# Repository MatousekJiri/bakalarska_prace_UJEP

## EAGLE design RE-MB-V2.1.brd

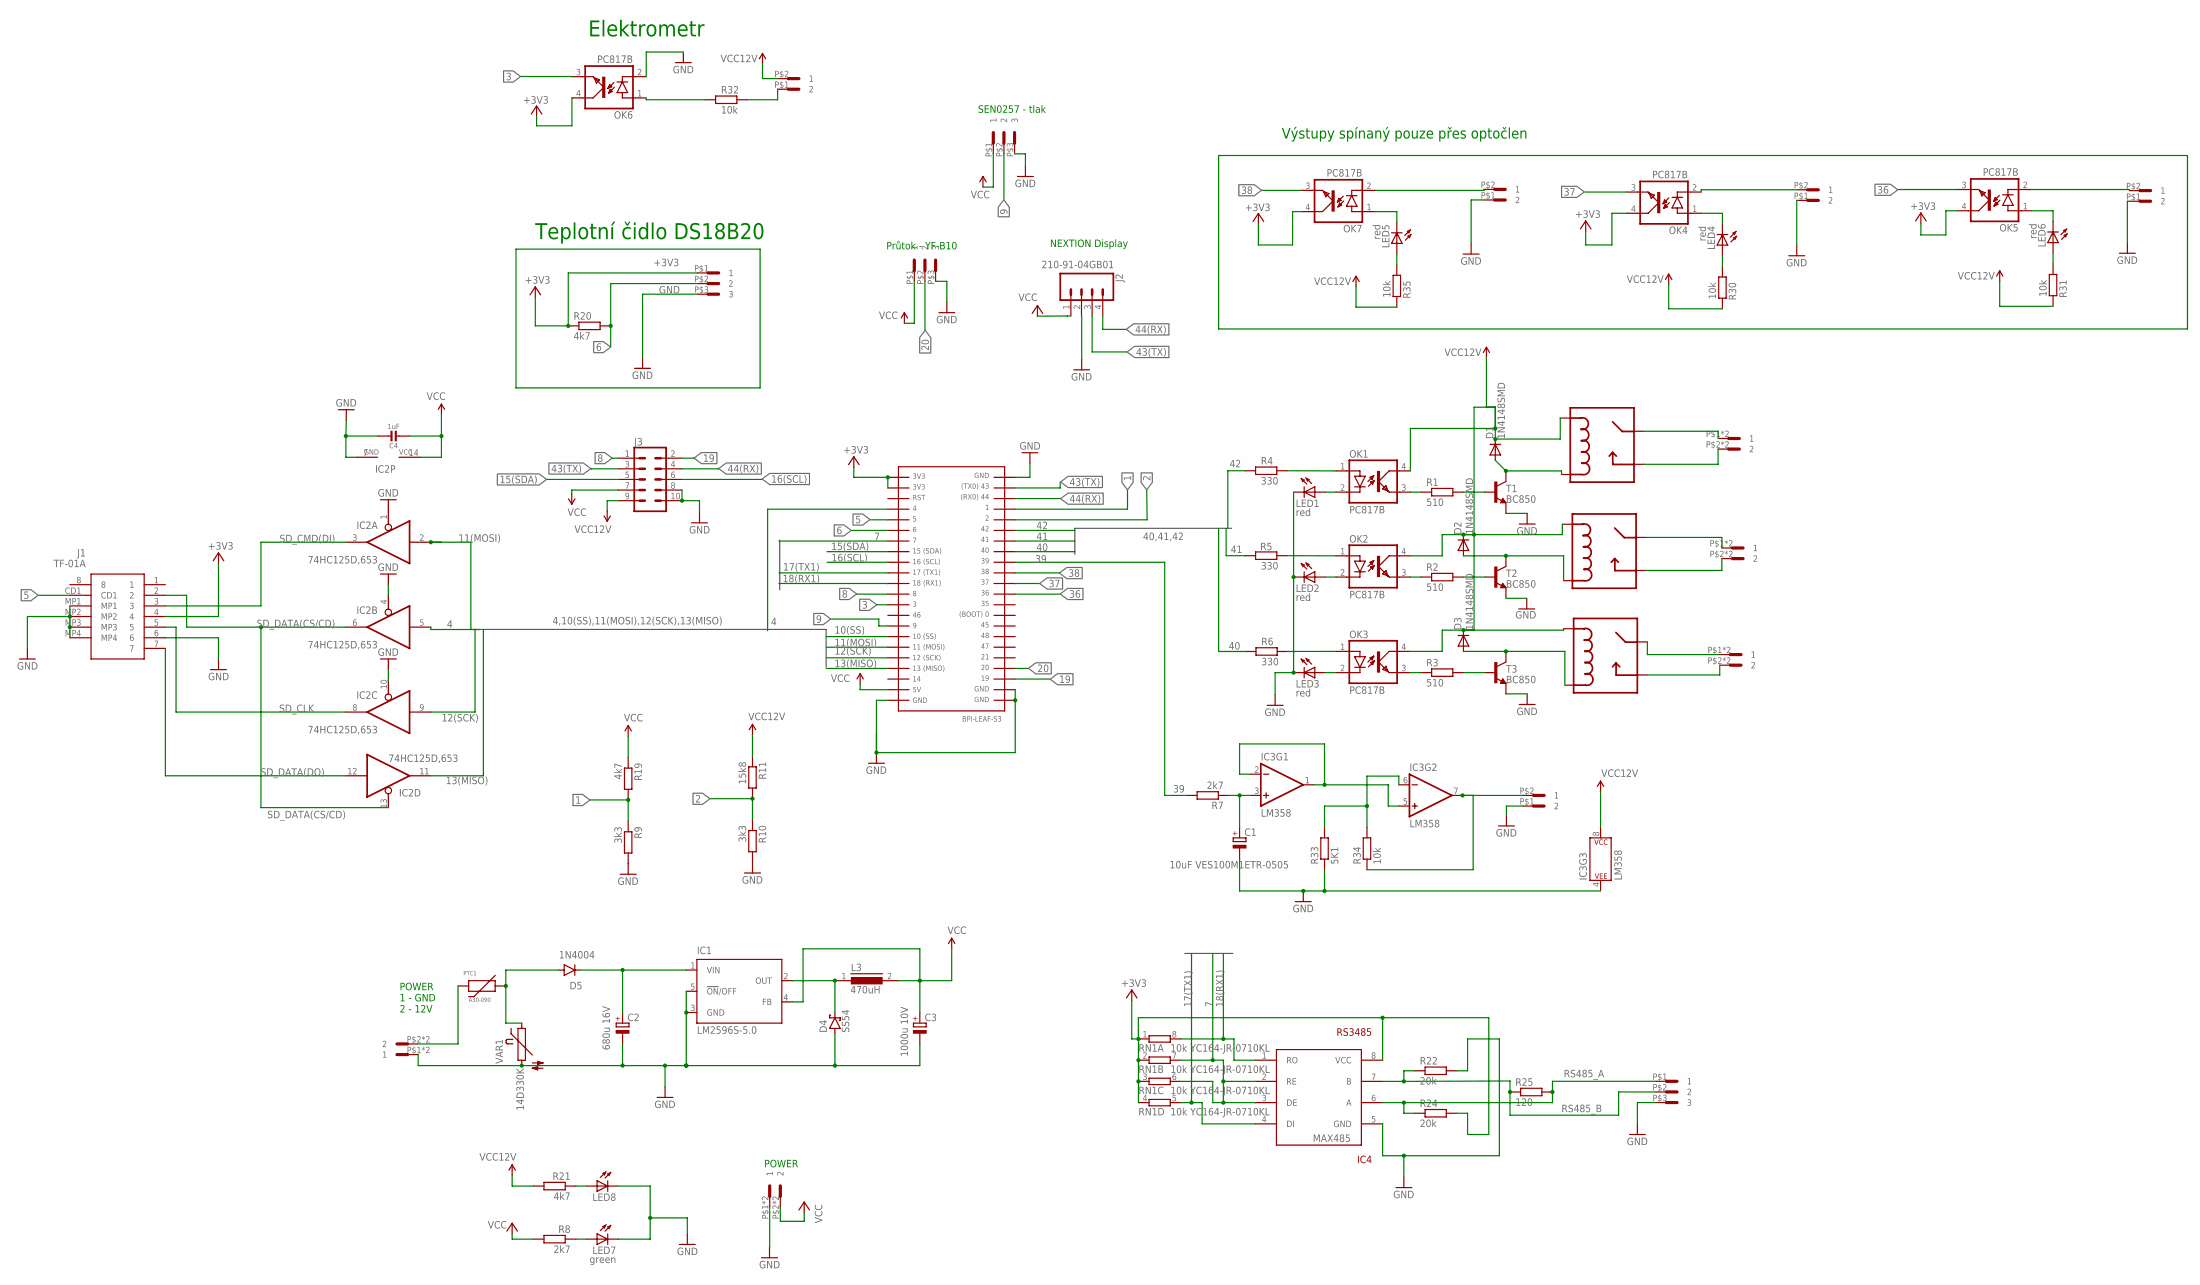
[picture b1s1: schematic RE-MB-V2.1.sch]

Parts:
BPI: BPI-LEAF-S3
C1: 10uF VES100M1ETR-0505; PANASONIC_C
C2: 680u 16V; 153CLV-1010
C3: 1000u 10V; 153CLV-1010
C4: 1uF; 0805-NO
D1, D2, D3: 1N4148SMD; DO214AC
D4: SS54; SMB
D5: 1N4004; DO41-10
IC1: LM2596S-5.0; TO263-5
IC2: 74HC125D,653; SO14
IC3: LM358; SO08
IC4: RS3485; MAX485
J1: TF-01A; TF01A
J2: 210-91-04GB01; 1X04
J3: CONN_05X2RAF; 2X5-RAF
K1, K2, K3: HF49FD/012-1H11; HF49FD/024-1H11
L3: 470uH; DR127
LED1, LED2, LED3, LED4, LED5, LED6: red; CHIPLED_0805
LED7, LED8: green; CHIPLED_0805
OK1, OK2, OK3, OK4, OK5, OK6, OK7: PC817B; DIL04
PTC1: A30-090; PK250-240
R1, R2, R3: 510; M0805
R4, R5, R6: 330; M0805
R7: 2k7; R0805
R8: 2k7; M0805
R9, R10: 3k3; M0805
R11: 15k8; M0805
R19, R20, R21: 4k7; M0805
R22, R24: 20k; R0805
R25: 120; R0805
R30, R31, R32, R35: 10k; M0805
R33: 5K1; R0805
R34: 10k; R0805
RN1: 10k YC164-JR-0710KL; 0603-ARV
T1, T2, T3: BC850; SOT23
U$2, U$4, U$5, U$6, U$7: DG235-5.0
U$3, U$10, U$12, U$16: SPTA1/3-5,0
U$8, U$9, U$13, U$14, U$15: SPTA1/2-5,0
VAR1: 14D330K; S10K11

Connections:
1: BPI.26, R9.1, R19.2
2: BPI.27, R10.1, R11.2
3: BPI.13, OK6.3 (EMIT)
4: BPI.4, IC2.5 (I)
5: BPI.5, J1.CD1
6: BPI.6, R20.2, U$3.P$2 (2)
7: BPI.7, IC4.2 (RE), IC4.3 (DE), RN1.6 (2), RN1.7 (2)
8: BPI.12, J3.1
9: BPI.15, U$12.P$2 (2)
10(SS): BPI.16
11(MOSI): BPI.17, IC2.2 (I)
12(SCK): BPI.18, IC2.9 (I)
13(MISO): BPI.19, IC2.11 (O)
15(SDA): BPI.8, J3.5
16(SCL): BPI.9, J3.6
17(TX1): BPI.10, IC4.4 (DI), RN1.5 (2)
18(RX1): BPI.11, IC4.1 (RO), RN1.8 (2)
19: BPI.42, J3.2
20: BPI.41, U$16.P$2 (2)
36: BPI.34, OK5.3 (EMIT)
37: BPI.33, OK4.3 (EMIT)
38: BPI.32, OK7.3 (EMIT)
39: BPI.31, R7.2
40: BPI.30, R6.1
41: BPI.29, R5.1
42: BPI.28, R4.1
43(TX): BPI.24, J2.3, J3.3
44(RX): BPI.25, J2.4, J3.4
+3V3: BPI.1, BPI.2, IC4.8 (VCC), J1.4, OK4.4 (COL), OK5.4 (COL), OK6.4 (COL), OK7.4 (COL), R20.1, R24.2, RN1.1, RN1.2 (1), RN1.3 (1), RN1.4 (1), U$3.P$1 (1)
GND: BPI.22, BPI.23, BPI.43, BPI.44, C1.-, C2.-, C3.-, C4.2, D4.A, IC1.3 (GND), IC1.5 (!ON!/OFF), IC2.1 (OE), IC2.4 (OE), IC2.7 (GND), IC2.10 (OE), IC3.4 (P$V-), IC4.5 (GND), J1.6, J1.MP1, J1.MP2, J1.MP3, J1.MP4, J2.2, J3.8, J3.10, LED1.C, LED2.C, LED3.C, LED7.C, LED8.C, OK6.2 (C), R9.2, R10.2, R22.2, R33.1, T1.2 (E), T2.2 (E), T3.2 (E), U$2.P$1 (1), U$2.P$3 (1), U$3.P$3 (3), U$6.P$1 (1), U$6.P$3 (1), U$8.P$1 (2), U$10.P$3 (3), U$12.P$3 (3), U$13.P$1 (2), U$14.P$1 (2), U$15.P$1 (2), U$16.P$3 (3), VAR1.2
GND1: OK4.2 (C), U$13.P$2 (1)
unnamed: PTC1.P$1, U$2.P$2 (2), U$2.P$4 (2)
unnamed: K1.P$1, U$4.P$1 (1), U$4.P$3 (1)
unnamed: D5.A, PTC1.P$2, VAR1.1
unnamed: K1.P$2, U$4.P$2 (2), U$4.P$4 (2)
unnamed: K2.P$1, U$5.P$1 (1), U$5.P$3 (1)
unnamed: K2.P$2, U$5.P$2 (2), U$5.P$4 (2)
unnamed: K3.P$1, U$7.P$1 (1), U$7.P$3 (1)
unnamed: K3.P$2, U$7.P$2 (2), U$7.P$4 (2)
unnamed: OK7.2 (C), U$15.P$2 (1)
unnamed: LED4.C, OK4.1 (A)
unnamed: LED4.A, R30.1
unnamed: OK5.2 (C), U$14.P$2 (1)
unnamed: LED6.C, OK5.1 (A)
unnamed: LED6.A, R31.1
unnamed: OK6.1 (A), R32.1
unnamed: LED1.A, OK1.2 (C)
unnamed: D1.A, K1.P$4, T1.3 (C)
unnamed: OK1.3 (EMIT), R1.1
unnamed: C1.+, IC3.3 (+IN), R7.1
unnamed: IC3.1 (OUT), IC3.2 (-IN), IC3.5 (+IN)
unnamed: R1.2, T1.1 (B)
unnamed: R32.2, U$9.P$1 (2)
unnamed: LED7.A, R8.1
unnamed: OK1.1 (A), R4.2
unnamed: LED8.A, R21.1
unnamed: D4.C, IC1.2 (OUT), L3.1
unnamed: IC3.6 (-IN), R33.2, R34.2
unnamed: IC3.7 (OUT), R34.1, U$8.P$2 (1)
unnamed: LED2.A, OK2.2 (C)
unnamed: LED3.A, OK3.2 (C)
unnamed: OK3.1 (A), R6.2
unnamed: OK2.1 (A), R5.2
unnamed: OK2.3 (EMIT), R2.1
unnamed: OK3.3 (EMIT), R3.1
unnamed: R3.2, T3.1 (B)
unnamed: R2.2, T2.1 (B)
unnamed: D2.A, K2.P$4, T2.3 (C)
unnamed: D3.A, K3.P$4, T3.3 (C)
unnamed: LED5.C, OK7.1 (A)
unnamed: LED5.A, R35.1
RS485_A: IC4.6 (A), R24.1, R25.2, U$10.P$1 (1)
RS485_B: IC4.7 (B), R22.1, R25.1, U$10.P$2 (2)
SD_CLK: IC2.8 (O), J1.5
SD_CMD(DI): IC2.3 (O), J1.3
SD_DATA(CS/CD): IC2.6 (O), IC2.13 (OE), J1.2
SD_DATA(DO): IC2.12 (I), J1.7
VCC: BPI.21, C3.+, C4.1, IC1.4 (FB), IC2.14 (VCC), J2.1, J3.7, L3.2, R8.2, R19.1, U$6.P$2 (2), U$6.P$4 (2), U$12.P$1 (1), U$16.P$1 (1)
VCC12V: C2.+, D1.C, D2.C, D3.C, D5.C, IC1.1 (VIN), IC3.8 (P$V+), J3.9, K1.P$3, K2.P$3, K3.P$3, OK1.4 (COL), OK2.4 (COL), OK3.4 (COL), R11.1, R21.2, R30.2, R31.2, R35.2, U$9.P$2 (1)

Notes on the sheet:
Výstupy spínaný pouze přes optočlen
Průtok - YF-B10
NEXTION Display
POWER 1 - GND 2 - 12V
Teplotní čidlo DS18B20
POWER
Elektrometr
SEN0257 - tlak

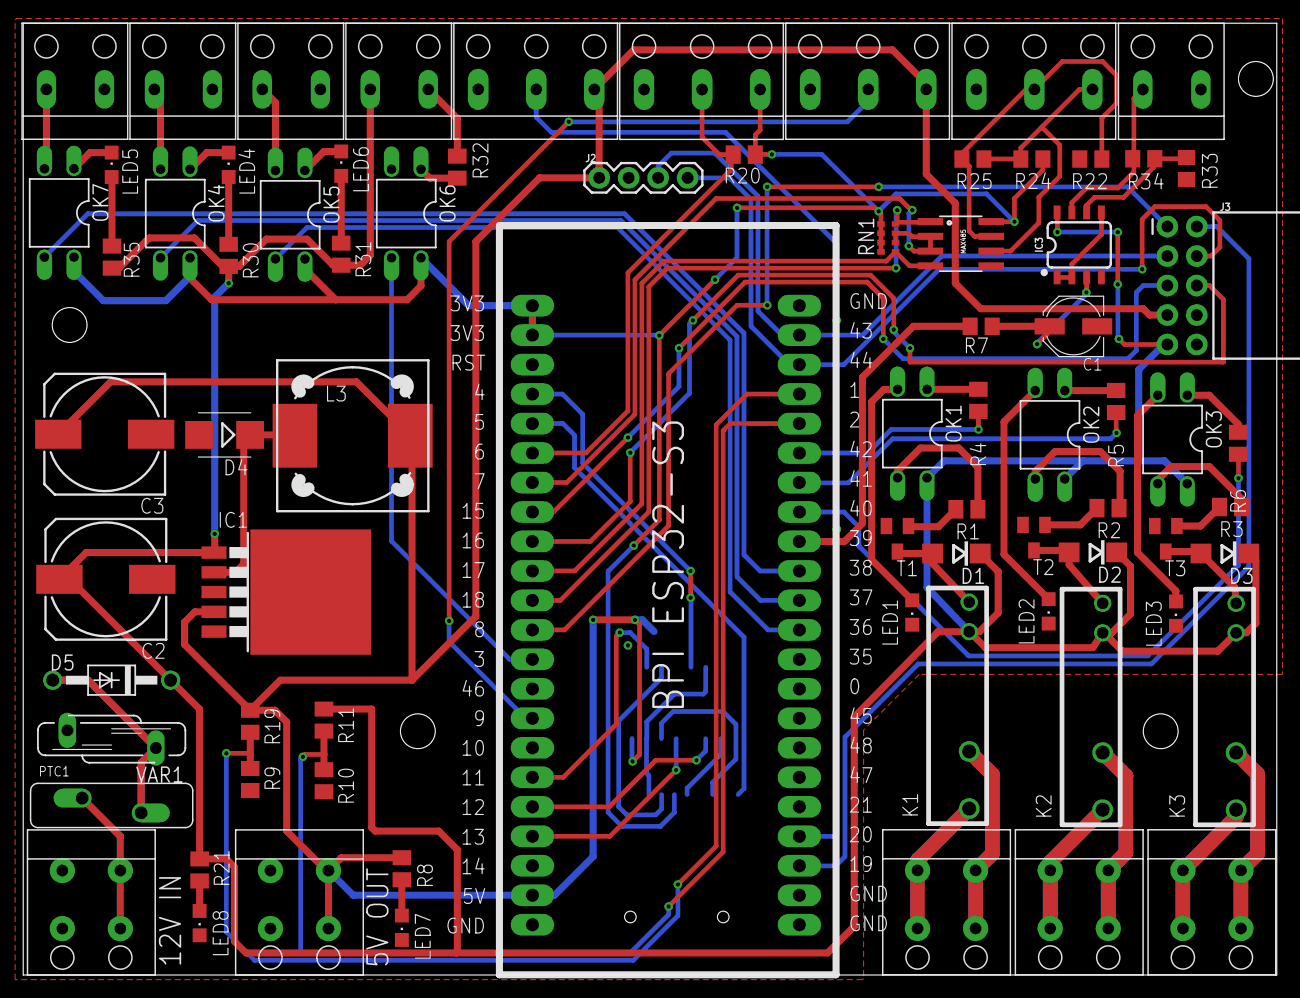
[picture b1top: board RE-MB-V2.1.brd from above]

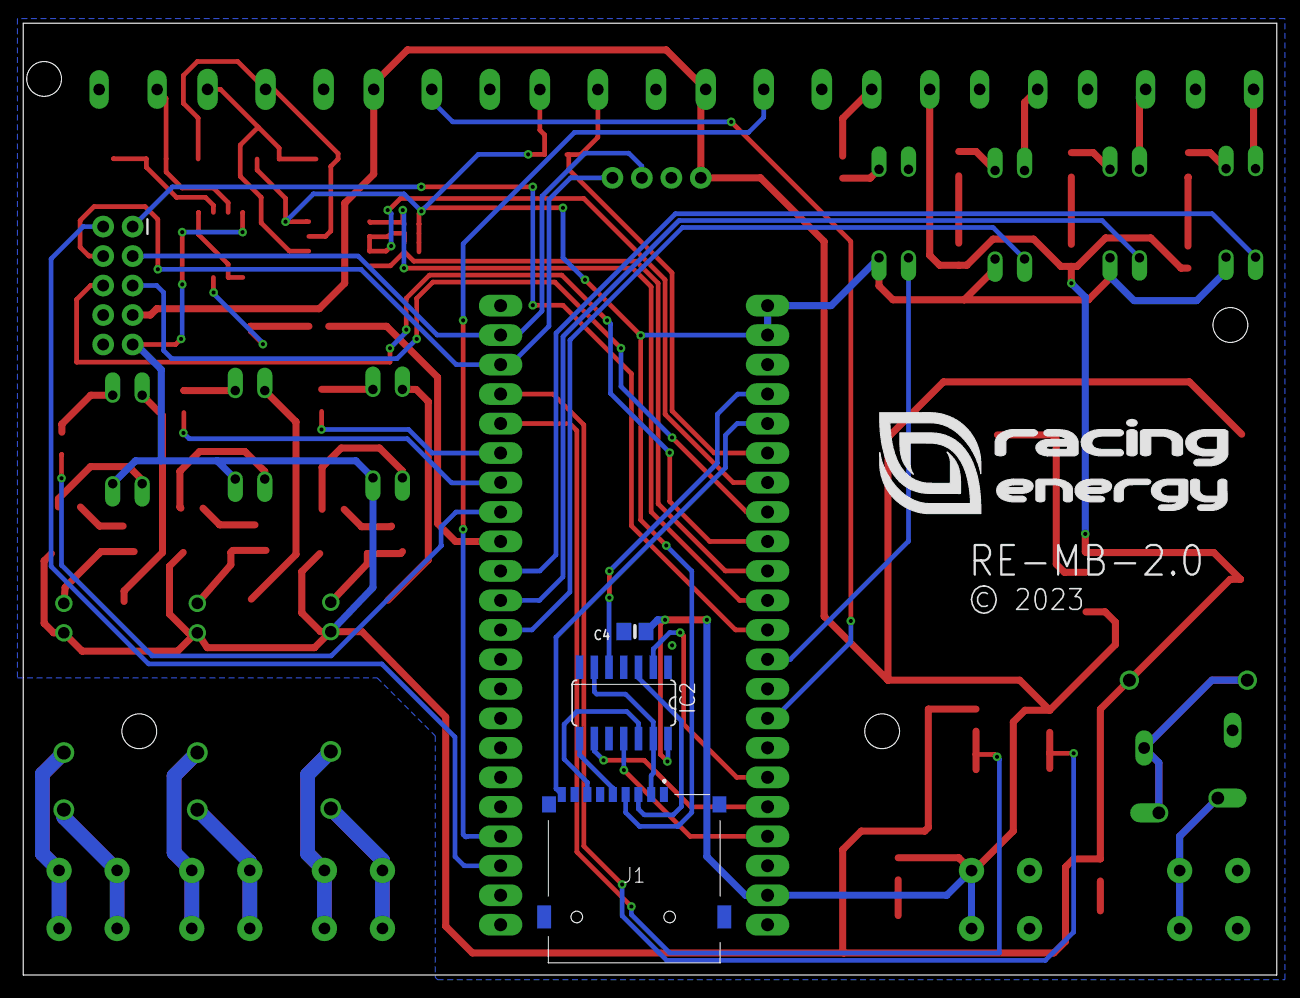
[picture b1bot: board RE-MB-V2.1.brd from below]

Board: 2 copper layers, 108.0 x 82.0 mm, 79 parts (3 on the bottom side), 78 nets.

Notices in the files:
RE-MB-V2.1.brd:
© 2023
parts and their libraries:
SparkFun-IC-Amplifiers: Licensing: Creative Commons ShareAlike 4.0 International - https://creativecommons.org/licenses/by-sa/4.0
microbuilder: This work is placed in the public domain, and may be freely used for commercial and non-commercial work with the following conditions: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
